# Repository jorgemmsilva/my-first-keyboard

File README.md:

# My first keyboard

My first attempt at designing my own keyboard.

I used [corney-island](https://github.com/ceoloide/corney-island/blob/main/package.json) as the base for this build.

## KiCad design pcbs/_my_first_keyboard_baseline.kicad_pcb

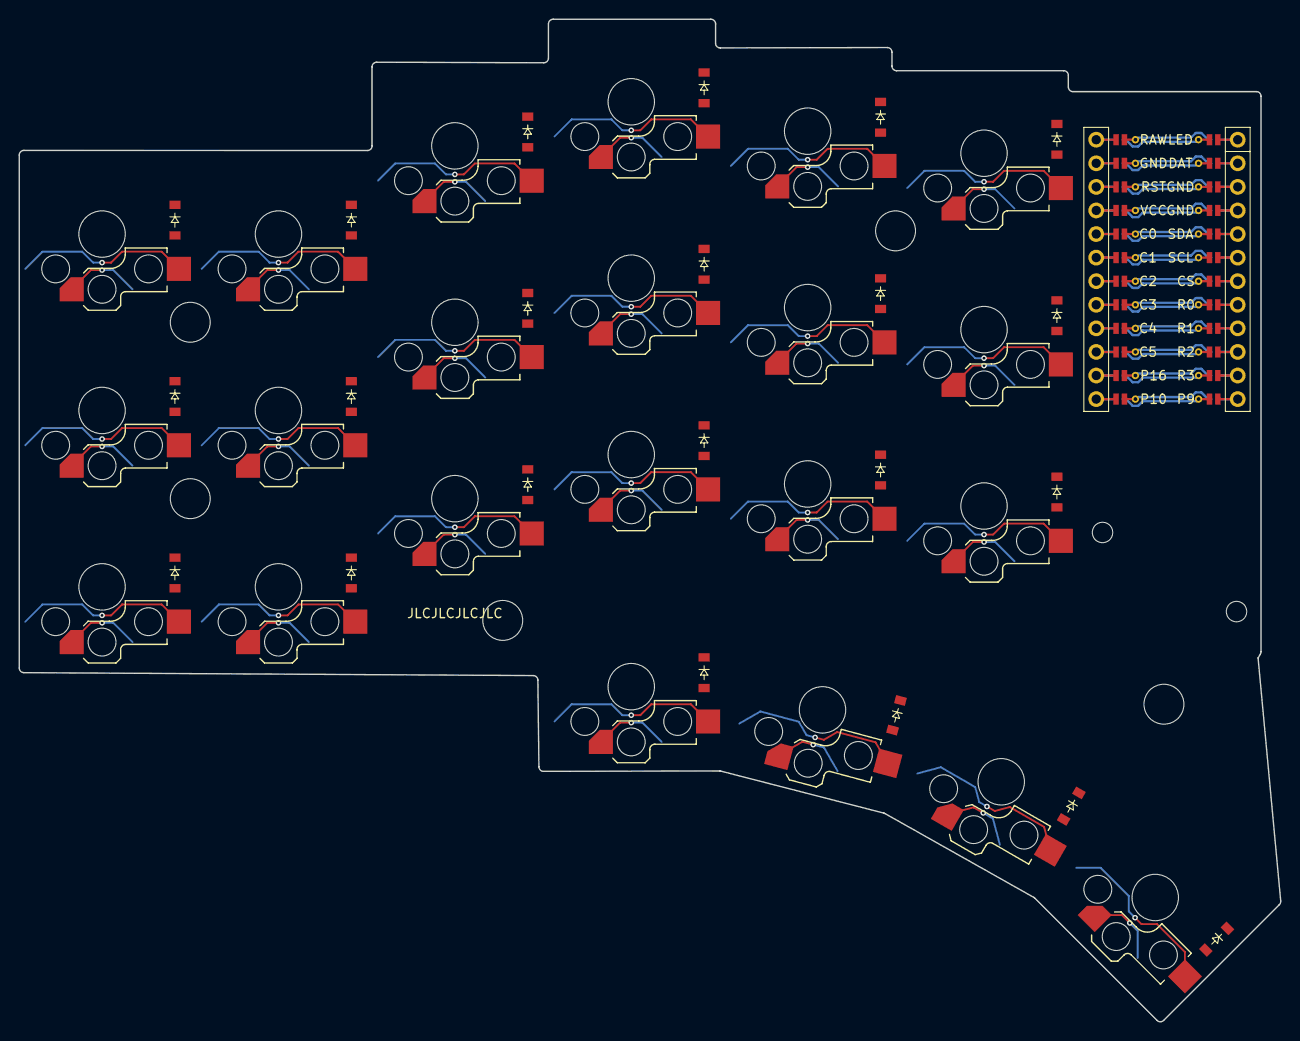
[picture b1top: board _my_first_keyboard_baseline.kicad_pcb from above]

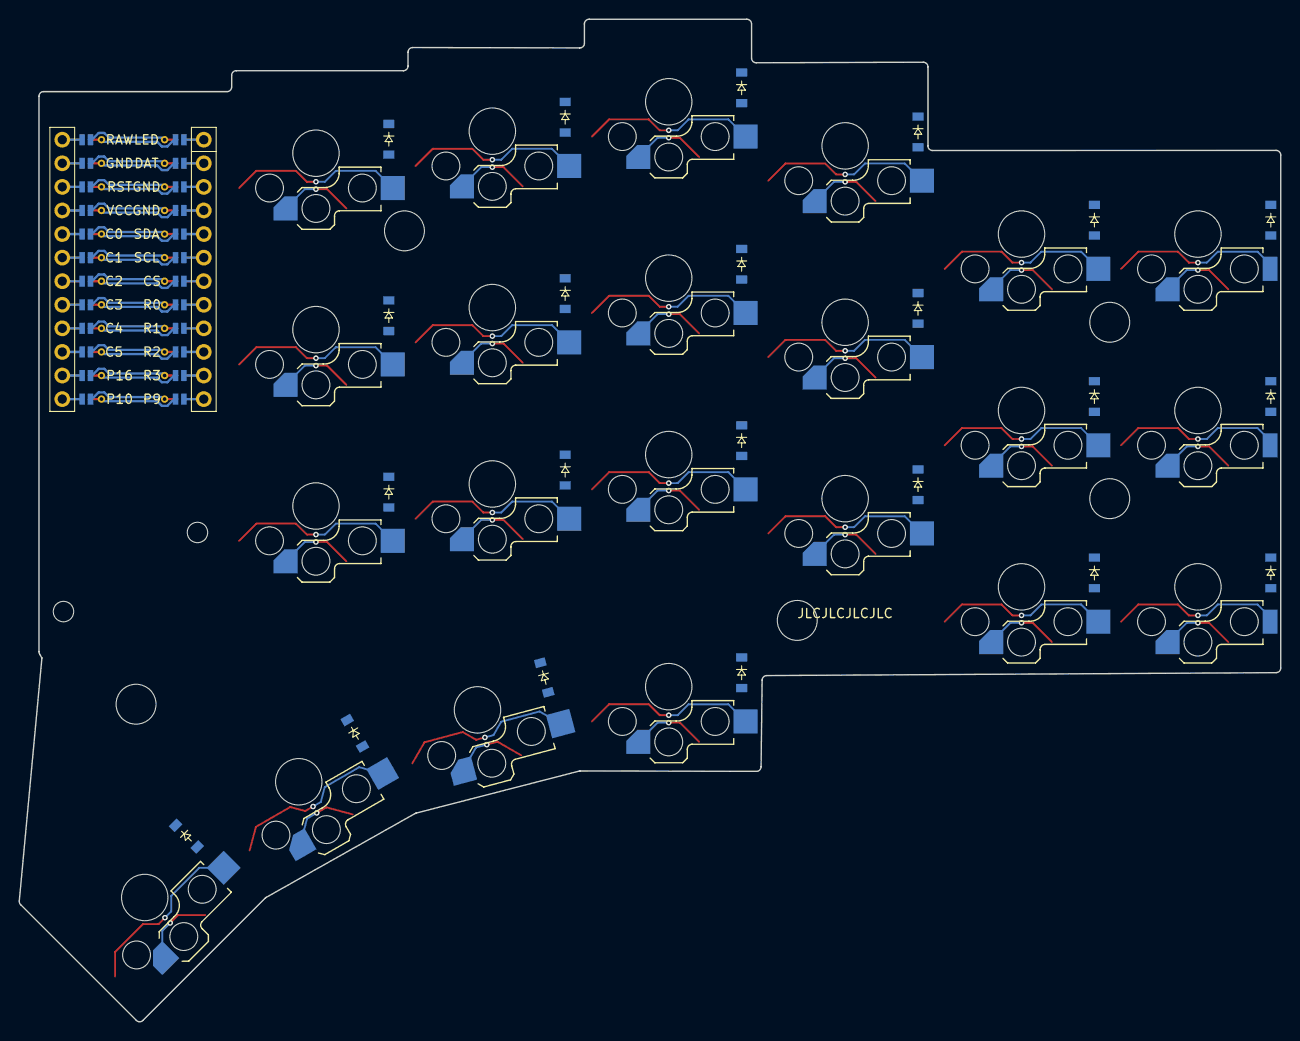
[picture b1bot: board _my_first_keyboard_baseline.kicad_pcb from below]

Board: 2 copper layers, 135.9 x 108.0 mm, 74 parts (44 on the bottom side), 33 nets.

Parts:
D1, D2, D3, D4, D5, D6, D7, D8, D9, D10, D11, D12, D13, D14, D15, D16, D17, D18, D19, D20, D21, D22, D23, D24, D25, D26, D27, D28, D29, D30, D31, D32, D33, D34, D35, D36, D37, D38, D39, D40, D41, D42, D43, D44: diode_tht_sod123
MCU1: mcu_nice_nano
MH1, MH2, MH3, MH4, MH5, MH6, MH7: mounting_hole_npth
S1, S2, S3, S4, S5, S6, S7, S8, S9, S10, S11, S12, S13, S14, S15, S16, S17, S18, S19, S20, S21, S22: switch_choc_v1_v2

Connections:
C0: MCU1.120, S1.1, S2.1, S3.1
C1: MCU1.119, S4.1, S5.1, S6.1
C2: MCU1.118, S7.1, S8.1, S9.1, S19.1
C3: MCU1.117, S10.1, S11.1, S12.1, S20.1
C4: MCU1.116, S13.1, S14.1, S15.1, S21.1
C5: MCU1.115, S16.1, S17.1, S18.1, S22.1
GND: MCU1.103, MCU1.104, MCU1.123
R0: D3.1, D6.1, D9.1, D12.1, D15.1, D18.1, D25.1, D28.1, D31.1, D34.1, D37.1, D40.1, MCU1.108
R1: D2.1, D5.1, D8.1, D11.1, D14.1, D17.1, D24.1, D27.1, D30.1, D33.1, D36.1, D39.1, MCU1.109
R2: D1.1, D4.1, D7.1, D10.1, D13.1, D16.1, D23.1, D26.1, D29.1, D32.1, D35.1, D38.1, MCU1.110
R3: D19.1, D20.1, D21.1, D22.1, D41.1, D42.1, D43.1, D44.1, MCU1.111
far_home_B: D21.2, S21.2
farest_home_B: D22.2, S22.2
index_bottom_B: D13.2, S13.2
index_home_B: D14.2, S14.2
index_top_B: D15.2, S15.2
inner_bottom_B: D16.2, S16.2
inner_home_B: D17.2, S17.2
inner_top_B: D18.2, S18.2
mid_home_B: D20.2, S20.2
middle_bottom_B: D10.2, S10.2
middle_home_B: D11.2, S11.2
middle_top_B: D12.2, S12.2
near_home_B: D19.2, S19.2
outer_bottom_B: D1.2, S1.2
outer_home_B: D2.2, S2.2
outer_top_B: D3.2, S3.2
pinky_bottom_B: D4.2, S4.2
pinky_home_B: D5.2, S5.2
pinky_top_B: D6.2, S6.2
ring_bottom_B: D7.2, S7.2
ring_home_B: D8.2, S8.2
ring_top_B: D9.2, S9.2

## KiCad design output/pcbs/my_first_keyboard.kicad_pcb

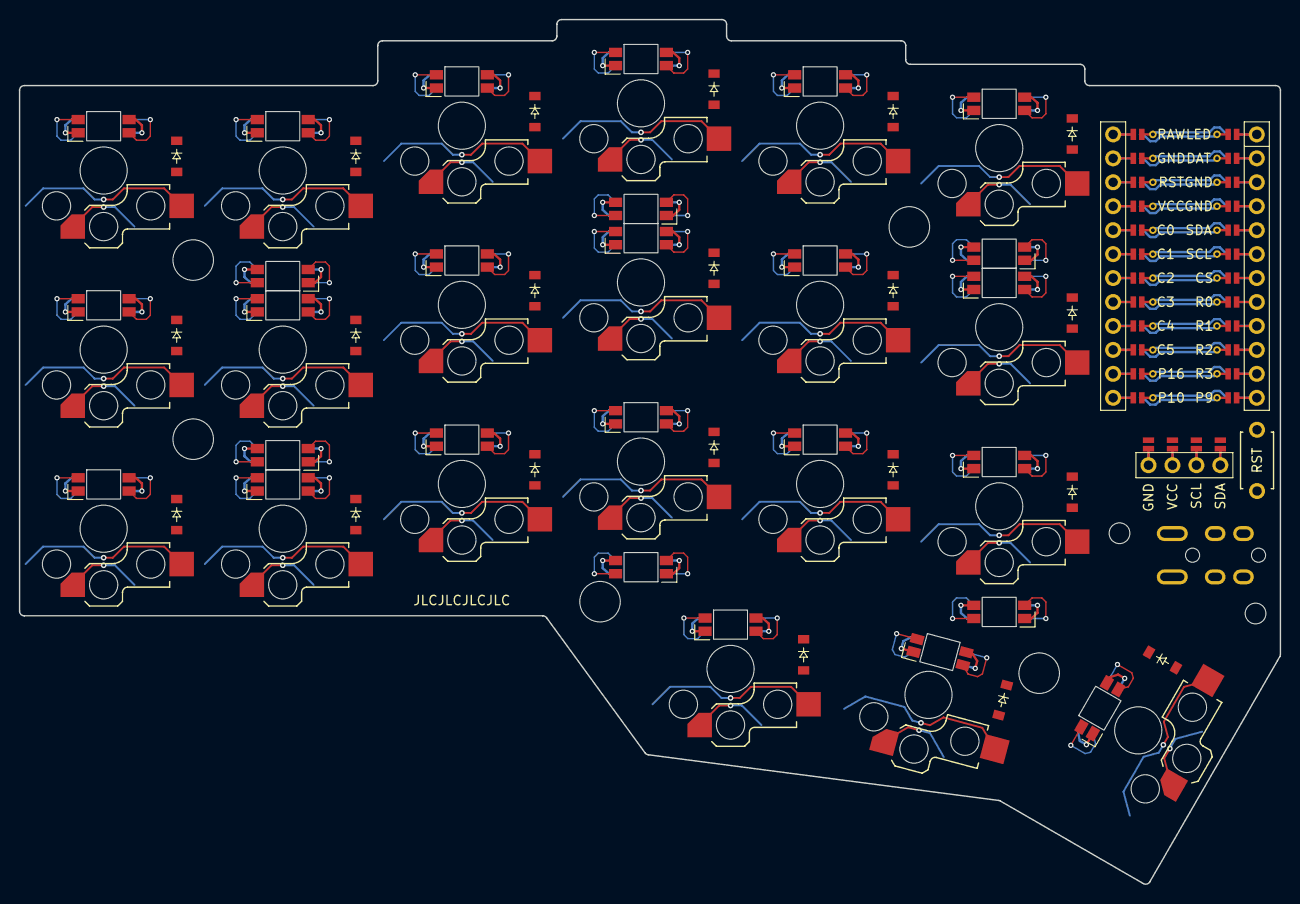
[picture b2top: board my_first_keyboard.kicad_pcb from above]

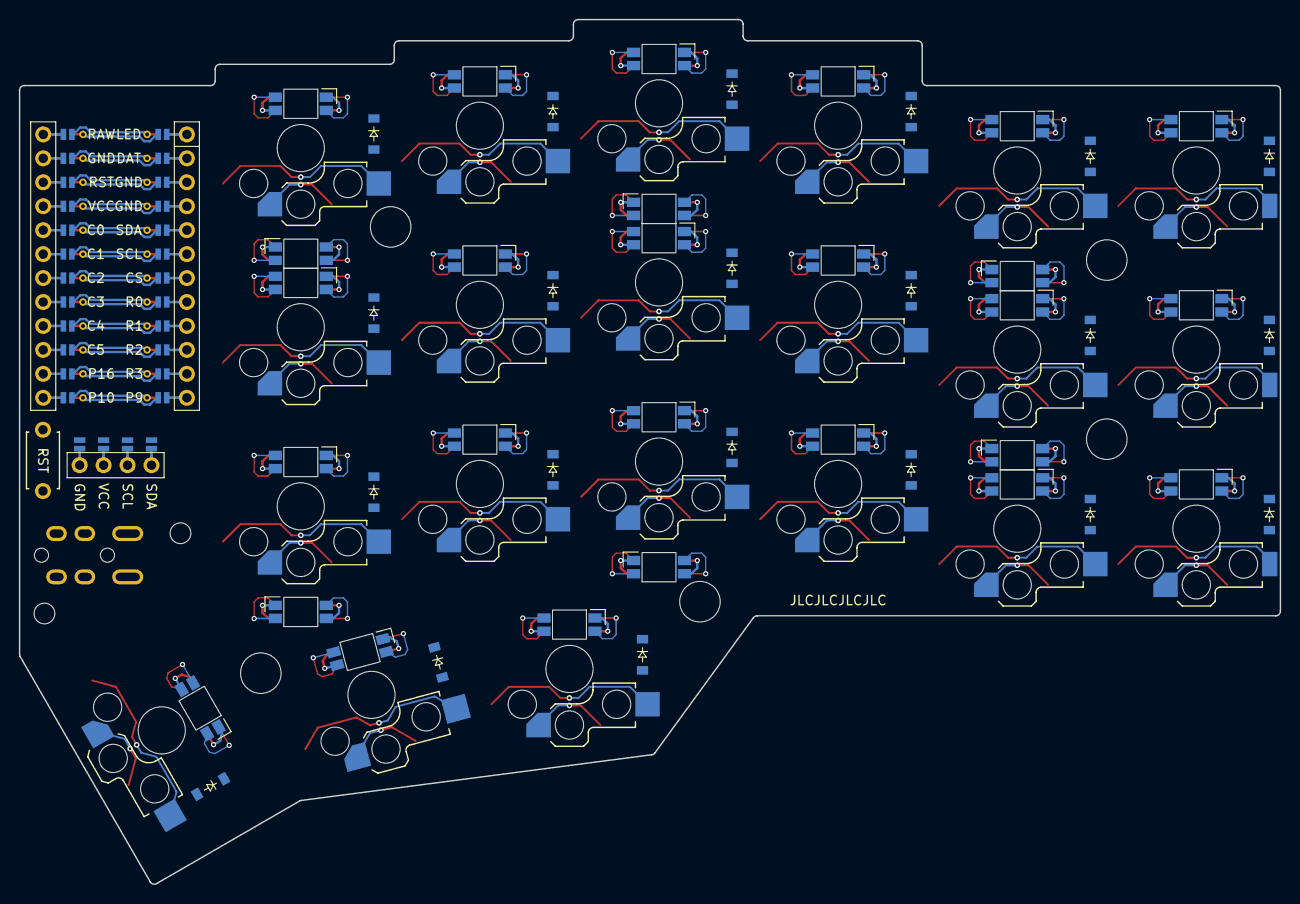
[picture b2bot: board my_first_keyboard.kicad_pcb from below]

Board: 2 copper layers, 133.8 x 91.7 mm, 101 parts (69 on the bottom side), 68 nets.

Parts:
D1, D2, D3, D4, D5, D6, D7, D8, D9, D10, D11, D12, D13, D14, D15, D16, D17, D18, D19, D20, D21, D22, D23, D24, D25, D26, D27, D28, D29, D30, D31, D32, D33, D34, D35, D36, D37, D38, D39, D40, D41, D42: diode_tht_sod123
DISP1: display_ssd1306
LED1, LED2, LED3, LED4, LED5, LED6, LED7, LED8, LED9, LED10, LED11, LED12, LED13, LED14, LED15, LED16, LED17, LED18, LED19, LED20, LED21: led_SK6812mini-e (per-key, reversible)
LED22, LED23, LED24, LED25, LED26, LED27: led_SK6812mini-e (underglow, reversible)
MCU1: mcu_nice_nano
MH1, MH2, MH3, MH4, MH5, MH6, MH7: mounting_hole_npth
RST1: reset_switch_tht_top
S1, S2, S3, S4, S5, S6, S7, S8, S9, S10, S11, S12, S13, S14, S15, S16, S17, S18, S19, S20, S21: switch_choc_v1_v2
TRRS1: trrs_pj320a (reversible, symmetric)

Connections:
C0: MCU1.120, S1.1, S2.1, S3.1
C1: MCU1.119, S4.1, S5.1, S6.1
C2: MCU1.118, S7.1, S8.1, S9.1
C3: MCU1.117, S10.1, S11.1, S12.1, S19.1
C4: MCU1.116, S13.1, S14.1, S15.1, S20.1
C5: MCU1.115, S16.1, S17.1, S18.1, S21.1
DAT: MCU1.102, TRRS1.3
DISP1_1: DISP1.1, DISP1.10, DISP1.23
DISP1_2: DISP1.2, DISP1.11, DISP1.22
DISP1_3: DISP1.3, DISP1.12, DISP1.21
DISP1_4: DISP1.4, DISP1.13, DISP1.20
GND: DISP1.14, DISP1.24, LED1.3, LED2.3, LED3.3, LED4.3, LED5.3, LED6.3, LED7.3, LED8.3, LED9.3, LED10.3, LED11.3, LED12.3, LED13.3, LED14.3, LED15.3, LED16.3, LED17.3, LED18.3, LED19.3, LED20.3, LED21.3, LED22.3, LED23.3, LED24.3, LED25.3, LED26.3, LED27.3, MCU1.103, MCU1.104, MCU1.123, RST1.2, TRRS1.2
LED: LED22.4, MCU1.101
LED_1: LED16.4, LED21.2
LED_2: LED16.2, LED17.4
LED_3: LED17.2, LED18.4
LED_4: LED15.4, LED18.2
LED_5: LED14.4, LED15.2
LED_6: LED13.4, LED14.2
LED_7: LED13.2, LED20.4
LED_8: LED19.4, LED20.2
LED_9: LED10.4, LED19.2
LED_10: LED10.2, LED11.4
LED_11: LED11.2, LED12.4
LED_12: LED9.4, LED12.2
LED_13: LED8.4, LED9.2
LED_14: LED7.4, LED8.2
LED_15: LED4.4, LED7.2
LED_16: LED4.2, LED5.4
LED_17: LED5.2, LED6.4
LED_18: LED3.4, LED6.2
LED_19: LED2.4, LED3.2
LED_20: LED1.4, LED2.2
R0: D3.1, D6.1, D9.1, D12.1, D15.1, D18.1, D24.1, D27.1, D30.1, D33.1, D36.1, D39.1, MCU1.108
R1: D2.1, D5.1, D8.1, D11.1, D14.1, D17.1, D23.1, D26.1, D29.1, D32.1, D35.1, D38.1, MCU1.109
R2: D1.1, D4.1, D7.1, D10.1, D13.1, D16.1, D22.1, D25.1, D28.1, D31.1, D34.1, D37.1, MCU1.110
R3: D19.1, D20.1, D21.1, D40.1, D41.1, D42.1, MCU1.111
RST: MCU1.122, RST1.1
SCL: DISP1.16, DISP1.26, MCU1.106
SDA: DISP1.17, DISP1.27, MCU1.105
ULED_1: LED22.2, LED23.4
ULED_2: LED23.2, LED24.4
ULED_3: LED24.2, LED25.4
ULED_4: LED25.2, LED26.4
ULED_5: LED26.2, LED27.4
ULED_6: LED21.4, LED27.2
VCC: DISP1.15, DISP1.25, LED1.1, LED2.1, LED3.1, LED4.1, LED5.1, LED6.1, LED7.1, LED8.1, LED9.1, LED10.1, LED11.1, LED12.1, LED13.1, LED14.1, LED15.1, LED16.1, LED17.1, LED18.1, LED19.1, LED20.1, LED21.1, LED22.1, LED23.1, LED24.1, LED25.1, LED26.1, LED27.1, MCU1.121, TRRS1.4
far_home_B: D21.2, S21.2
index_bottom_B: D13.2, S13.2
index_home_B: D14.2, S14.2
index_top_B: D15.2, S15.2
inner_bottom_B: D16.2, S16.2
inner_home_B: D17.2, S17.2
inner_top_B: D18.2, S18.2
mid_home_B: D20.2, S20.2
middle_bottom_B: D10.2, S10.2
middle_home_B: D11.2, S11.2
middle_top_B: D12.2, S12.2
near_home_B: D19.2, S19.2
outer_bottom_B: D1.2, S1.2
outer_home_B: D2.2, S2.2
outer_top_B: D3.2, S3.2
pinky_bottom_B: D4.2, S4.2
pinky_home_B: D5.2, S5.2
pinky_top_B: D6.2, S6.2
ring_bottom_B: D7.2, S7.2
ring_home_B: D8.2, S8.2
ring_top_B: D9.2, S9.2

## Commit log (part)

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2026-05-13 iteration
2026-05-15 functional 1
2026-05-16 using new corney island
2026-06-14 firmware
2026-06-15 fix firmware
2026-06-27 firmware working
2026-06-27 layout v1
2026-06-27 key combos
2026-06-28 minor layout customization
2026-06-30 layout iteration
